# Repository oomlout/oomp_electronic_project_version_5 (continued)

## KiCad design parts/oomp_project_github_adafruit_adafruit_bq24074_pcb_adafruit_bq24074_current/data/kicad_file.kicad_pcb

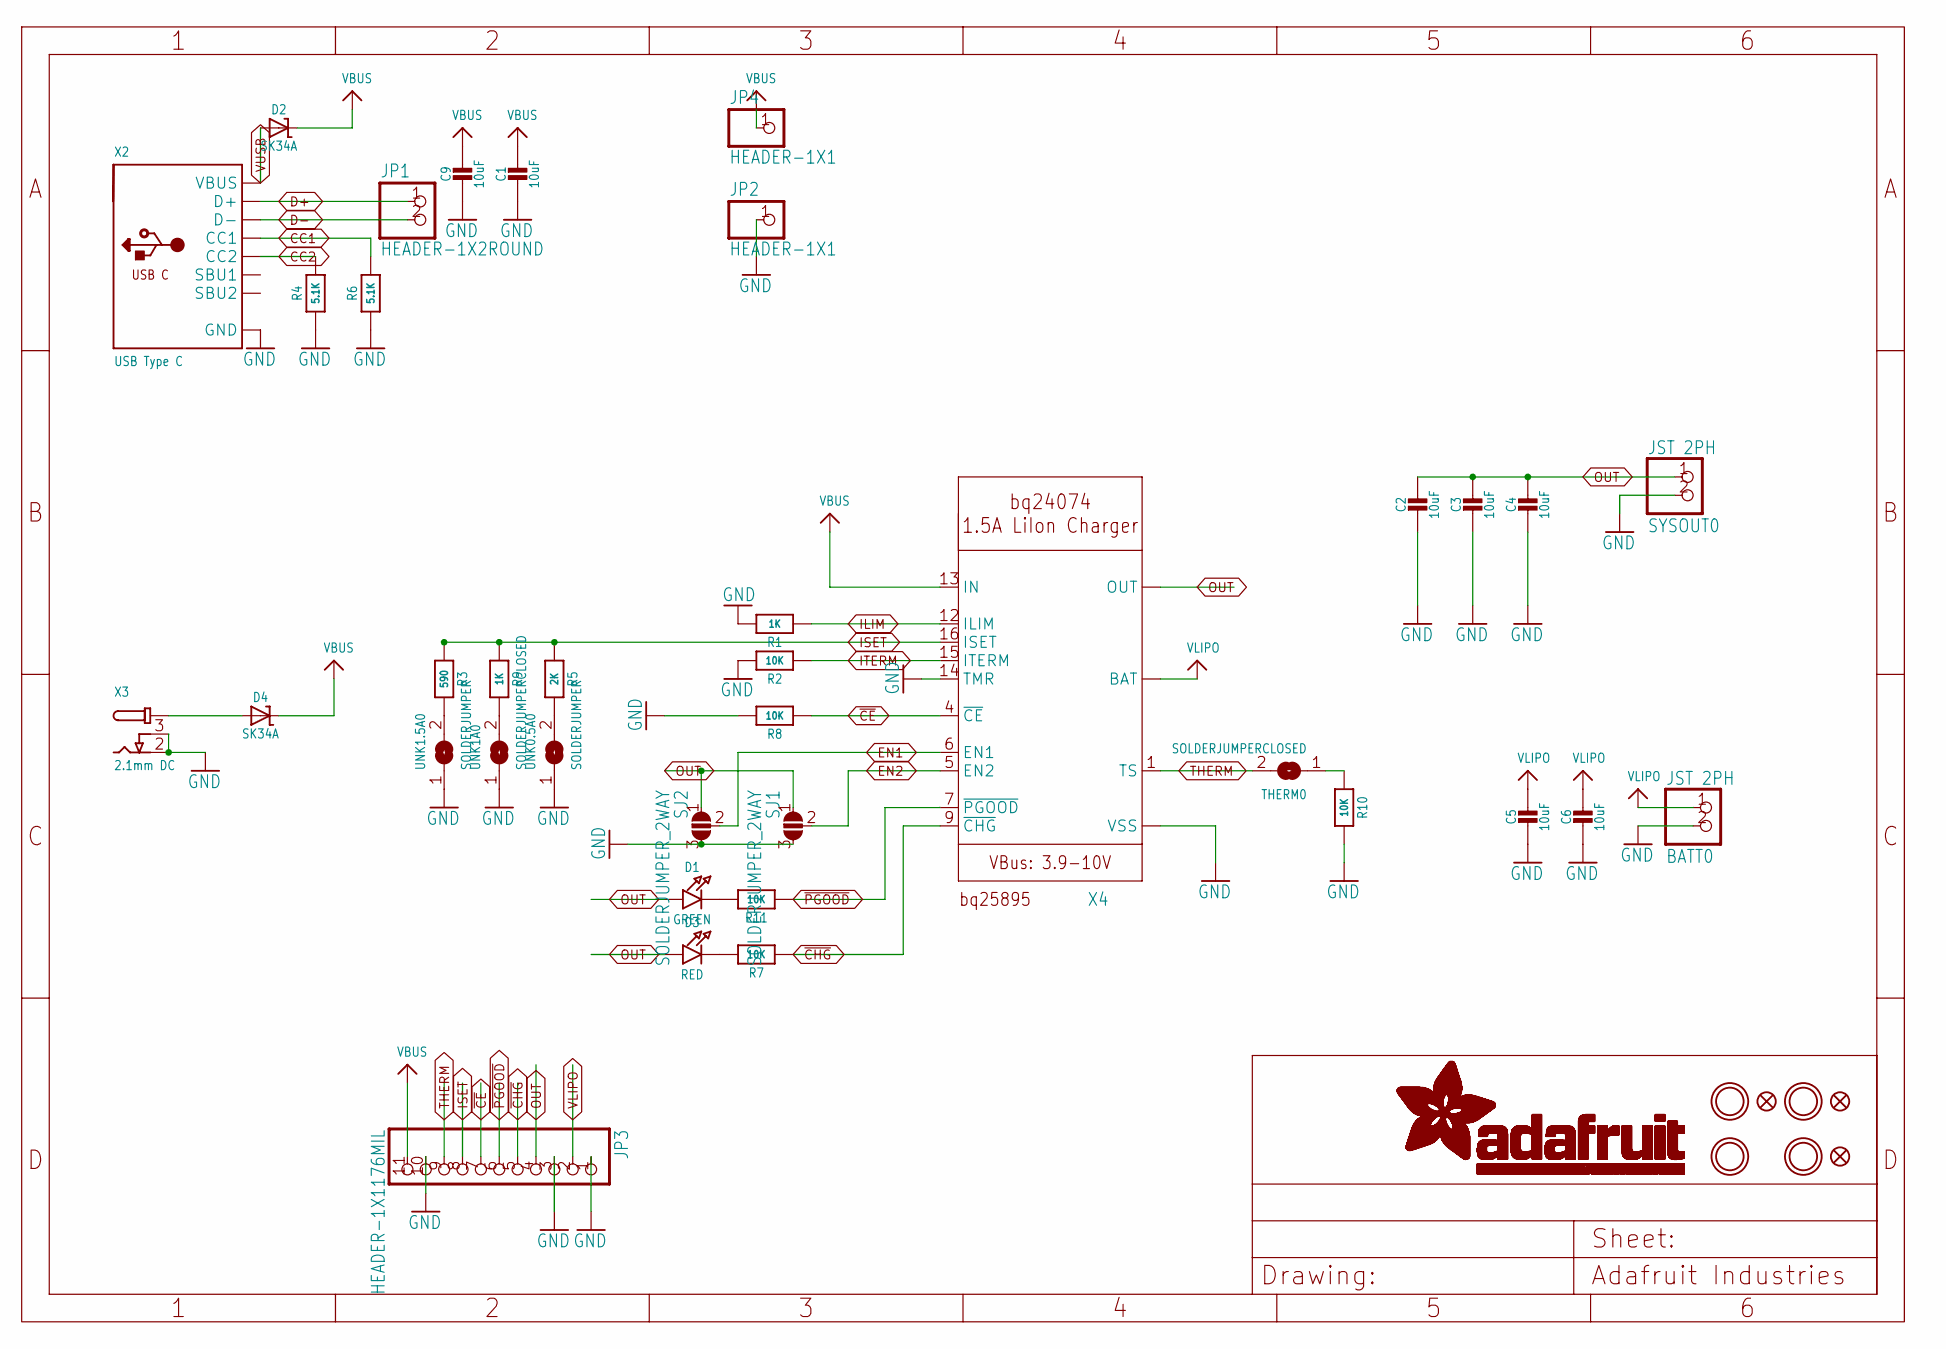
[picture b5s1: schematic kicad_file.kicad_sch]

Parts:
BATT0: JST 2PH; JST-PH-2-SMT-RA
C1, C2, C3, C4, C5, C6, C9: 10uF; 0805-NO
D1: GREEN; CHIPLED_0603
D2, D4: SK34A; SMADIODE
D3: RED; CHIPLED_0603
FID1, FID2, FID3: FIDUCIAL_1MM
JP1: HEADER-1X2ROUND; 1X02_ROUND
JP2, JP4: HEADER-1X1; 1X01_OVAL
JP3: HEADER-1X1176MIL; 1X11_ROUND_76
R1, R9: 1K; 0603-NO
R2, R7, R8, R10, R11: 10K; 0603-NO
R3: 590; 0603-NO
R4, R6: 5.1K; 0603-NO
R5: 2K; 0603-NO
SJ1, SJ2: SOLDERJUMPER_2WAY; SOLDERJUMPER_2WAY_OPEN_NOPASTE
SYSOUT0: JST 2PH; JST-PH-2-SMT-RA
THERM0: SOLDERJUMPERCLOSED; SOLDERJUMPER_CLOSEDWIRE
U$3, U$4, U$11, U$12: MOUNTINGHOLE2.5; MOUNTINGHOLE_2.5_PLATED
UNK0.5A0, UNK1.5A0: SOLDERJUMPER; SOLDERJUMPER_ARROW_NOPASTE
UNK1A0: SOLDERJUMPERCLOSED; SOLDERJUMPER_CLOSEDWIRE
X2: USB Type C; USB_C_CUSB31-CFM2AX-01-X
X3: 2.1mm DC; DCJACK_2MM_SMT
X4: BQ24074; QFN16_3MM

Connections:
CC1: R6.2, X2.A5 (CC1)
CC2: R4.2, X2.B5 (CC2)
D+: JP1.1, X2.A6 (D+), X2.B6 (D+)
D-: JP1.2, X2.A7 (D-), X2.B7 (D-)
EN1: SJ2.2, X4.6 (EN1)
EN2: SJ1.2, X4.5 (EN2)
GND: BATT0.2 (1), C1.2, C2.2, C3.2, C4.2, C5.2, C6.2, C9.2, JP2.1, JP3.1, JP3.3, JP3.10, R1.2, R2.2, R4.1, R6.1, R8.2, R10.2, SJ1.3, SJ2.3, SYSOUT0.2 (1), UNK0.5A0.1, UNK1.5A0.1, UNK1A0.1, X2.A1B12 (GND), X2.B1A12 (GND), X3.2 (GND), X3.3 (GNDBREAK), X4.8 (VSS), X4.14 (TMR), X4.THERMAL (VSS)
ILIM: R1.1, X4.12 (ILIM)
ISET: JP3.8, R3.1, R5.1, R9.1, X4.16 (ISET)
ITERM: R2.1, X4.15 (ITERM)
unnamed: D1.C, R11.2
unnamed: D4.A, X3.1 (PWR), X3.1' (PWR)
unnamed: D3.C, R7.2
unnamed: R3.2, UNK1.5A0.2
unnamed: R5.2, UNK0.5A0.2
unnamed: R9.2, UNK1A0.2
unnamed: R10.1, THERM0.1
OUT: C2.1, C3.1, C4.1, D1.A, D3.A, JP3.4, SJ1.1, SJ2.1, SYSOUT0.1 (2), X4.10 (OUT), X4.11 (OUT)
THERM: JP3.9, THERM0.2, X4.1 (TS)
VBUS: C1.1, C9.1, D2.C, D4.C, JP3.11, JP4.1, X4.13 (IN)
VLIPO: BATT0.1 (2), C5.1, C6.1, JP3.2, X4.2 (BAT), X4.3 (BAT)
VUSB: D2.A, X2.A4B9 (VBUS), X2.B4A9 (VBUS)
~CE: JP3.7, R8.1, X4.4 (~CE)
~CHG: JP3.5, R7.1, X4.9 (~CHG)
~PGOOD: JP3.6, R11.1, X4.7 (~PGOOD)

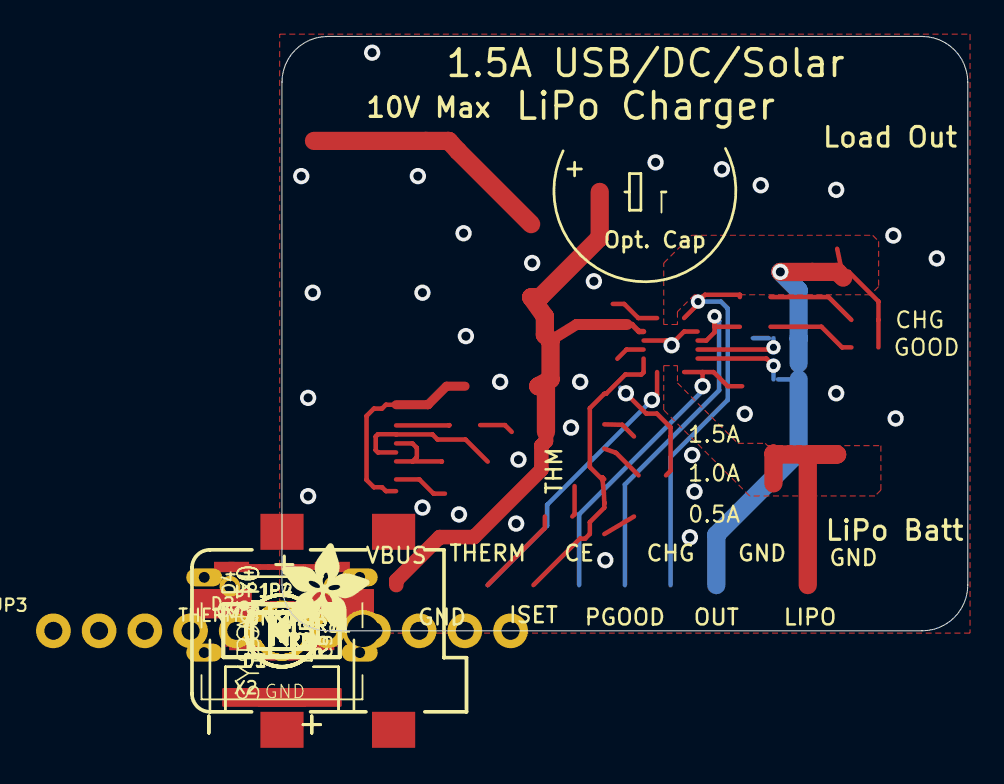
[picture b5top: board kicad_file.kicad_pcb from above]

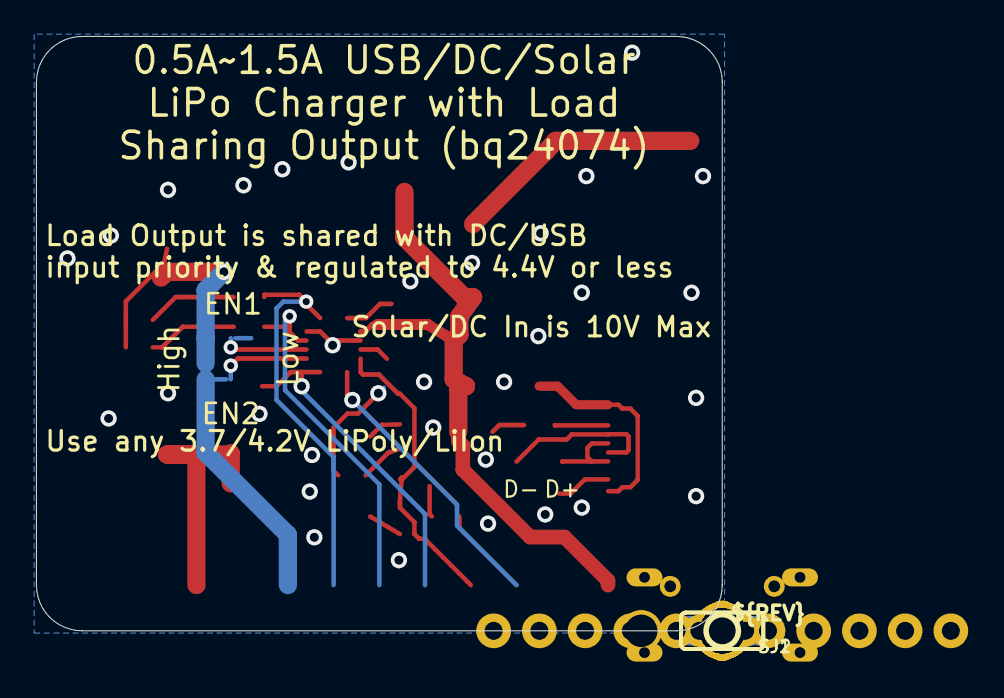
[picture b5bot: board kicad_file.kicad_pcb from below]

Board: 2 copper layers, 38.1 x 33.0 mm, 46 parts (3 on the bottom side), 25 nets.

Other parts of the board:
U$14: ADAFRUIT_5MM
U$18: PCBFEAT-REV-040

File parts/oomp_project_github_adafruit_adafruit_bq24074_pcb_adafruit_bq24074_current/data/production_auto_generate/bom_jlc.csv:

Comment,Designator,Footprint,LCSC Part #
,"JP2,JP4",Adafruit_BQ24074-import-fps:1X01_OVAL,C7501259
,JP1,Adafruit_BQ24074-import-fps:1X02_ROUND,C492401
,JP3,Adafruit_BQ24074-import-fps:1X11_ROUND_76,C2894934
,U$14,Adafruit_BQ24074-import-fps:ADAFRUIT_5MM,
,U$18,Adafruit_BQ24074-import-fps:PCBFEAT-REV-040,
,"UNK0.5A0,UNK1.5A0",Adafruit_BQ24074-import-fps:SOLDERJUMPER_ARROW_NOPASTE,
,"THERM0,UNK1A0",Adafruit_BQ24074-import-fps:SOLDERJUMPER_CLOSEDWIRE,
10K,"R2,R7,R8,R10,R11",Adafruit_BQ24074-import-fps:0603-NO,C98220
10uF,"C1,C2,C3,C4,C5,C6,C9",Adafruit_BQ24074-import-fps:0805-NO,
1K,"R1,R9",Adafruit_BQ24074-import-fps:0603-NO,C2907002
2.1mm DC,X3,Adafruit_BQ24074-import-fps:DCJACK_2MM_SMT,
2K,R5,Adafruit_BQ24074-import-fps:0603-NO,C22975
5.1K,"R4,R6",Adafruit_BQ24074-import-fps:0603-NO,C23186
590,R3,Adafruit_BQ24074-import-fps:0603-NO,
BQ24074,X4,Adafruit_BQ24074-import-fps:QFN16_3MM,
GREEN,D1,Adafruit_BQ24074-import-fps:CHIPLED_0603,
JST 2PH,"BATT0,SYSOUT0",Adafruit_BQ24074-import-fps:JST-PH-2-SMT-RA,
RED,D3,Adafruit_BQ24074-import-fps:CHIPLED_0603,
SK34A,"D2,D4",Adafruit_BQ24074-import-fps:SMADIODE,
USB Type C,X2,Adafruit_BQ24074-import-fps:USB_C_CUSB31-CFM2AX-01-X,

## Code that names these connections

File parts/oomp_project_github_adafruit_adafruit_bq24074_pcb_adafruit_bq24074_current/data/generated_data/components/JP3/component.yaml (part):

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      connected_to:
      - reference: '#U$8'
        pin_number: '1'
        pin_name: VLIPO
      - reference: '#U$9'
        pin_number: '1'
        pin_name: VLIPO
      - reference: '#U$10'
        pin_number: '1'
        pin_name: VLIPO
      - reference: '#U$13'
        pin_number: '1'
        pin_name: VLIPO
      - reference: BATT0
        pin_number: '1'
        pin_name: '2'
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        pin_name: '1'
      - reference: X4
        pin_number: '9'
        pin_name: ~{CHG}
    - number: '6'
      name: '6'
      electrical_type: passive
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        pin_name: '1'
      - reference: X4
        pin_number: '7'
        pin_name: ~{PGOOD}
    - number: '7'
      name: '7'
      electrical_type: passive
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        pin_name: '1'
      - reference: X4
        pin_number: '16'
        pin_name: ISET
    - number: '9'
      name: '9'
      electrical_type: passive
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    pin_name: VBUS
  - reference: '#U$8'
    pin_number: '1'
    pin_name: VLIPO
  - reference: '#U$9'
    pin_number: '1'
    pin_name: VLIPO
  - reference: '#U$10'
    pin_number: '1'
    pin_name: VLIPO
  - reference: '#U$13'
    pin_number: '1'
    pin_name: VLIPO
  - reference: '#U$15'
    pin_number: '1'
    pin_name: VBUS
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    pin_name: TMR
  - reference: X4
    pin_number: '16'
    pin_name: ISET
  - reference: X4
    pin_number: '2'
    pin_name: BAT
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    pin_name: ~{CE}
  - reference: X4
    pin_number: '7'
    pin_name: ~{PGOOD}
  - reference: X4
    pin_number: '8'
    pin_name: VSS
  - reference: X4
    pin_number: '9'
    pin_name: ~{CHG}
  - reference: X4
    pin_number: THERMAL
    pin_name: VSS
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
